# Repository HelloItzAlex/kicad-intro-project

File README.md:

# Kicad Intro Project

We will be creating an Astable timer circuit using a 555 timer, an LED, resistors, capacitors, and batteries. 555 timers can be used to generate stable and accurate oscillations or time delays. In our case, we will be using this [timer](https://www.ti.com/lit/ds/symlink/lm555.pdf?HQS=dis-dk-null-digikeymode-dsf-pf-null-wwe&ts=1630736989538&ref_url=https%253A%252F%252Fwww.ti.com%252Fgeneral%252Fdocs%252Fsuppproductinfo.tsp%253FdistId%253D10%2526gotoUrl%253Dhttps%253A%252F%252Fwww.ti.com%252Flit%252Fgpn%252Flm555)
 to run in Astable operation mode, which means that it will begin a free running oscillation. I recommend reading through the datasheet linked above, as lots of useful information can be found there! The frequency of the oscillations can be controlled by the value of resistors and capacitors that you choose to use in your circuit.  

The equation used to calculate the frequency is shown here:

## Create a new Kicad Project:
+ The documentation for Kicad can be found [here](https://docs.kicad.org/5.1/en/getting_started_in_kicad/getting_started_in_kicad.html), where there is a step-by-step tutorial on creating your first project.
+ Create a new project by clicking File->New->Project, and naming it.

## Create your schematic:
+ The first step to designing a PCB is creating the schematic. Open the Kicad Schematic software, “Eeschema”, by clicking on the button titled “Schematic Layout Editor”. Now you can begin to create your circuit!
+ There wil also be an example schematic included in the repository that can be used as a reference.
+ Begin placing components and wiring them together to create the circuit. Refer back to the [Kicad documentation](https://docs.kicad.org/5.1/en/getting_started_in_kicad/getting_started_in_kicad.html) for detailed instructions on how to place components and connect them together. All of  the components necessary for this tutorial are available in the Kicad component library. A list of the components you will need:
    + *1* LM555 Timer
    + *1* LED
    + *2* Resistors(1 10k Resistor, and 1 5k Resistor)
    + *2* Capacitors(1 0.01uF Capacitor, and 1 10uF Capacitor)
    + *2* 3V Single Cell Batteries
    + *2* VCC Labels
    + *2* GND Labels
    + *2* Power Flags
+  An example circuit for an Astable timer can be found in the datasheet(not including batteries):

+ Once you have finished making your circuit, run through these steps in order:
    1. Click on the Annotate Schematic symbol , and annotate all symbols in the schematic.
    2. Click on the Electrical Rules Check(ERC) symbol , and verify that you aren't violating any electrical rules.
    3. Click on the Assign PCB footprints to schematic symbol . Here, you will tell the PCB editor which physical footprint goes with each schematic symbol. It is up to you to make sure that the symbol has the corresponding footprint. The list of footprints that will be used:
        + *2* Battery:BatteryHolder_LINX_BAT-HLD-012-SMT
        + *2* Capacitor_SMD:C_0805_2012Metric
        + *2* Resistor_SMD:R_0805_2012Metric
        + *1* LED_SMD:LED_0805_2012Metric
        + *1* Package_SO:SOIC-8_3.9x4.9mm_P1.27mm (for the 555 timer)
    4. Click on the Generate Netlist symbol , and generate the netlist that will be used in the PCB editor, "PCBnew".
+ You have now finished with the Schematic design part of this project! Next, we will complete the PCB design in PCBnew

## Create your PCB Layout
+ Again, refer back to the [Kicad documentation](https://docs.kicad.org/5.1/en/getting_started_in_kicad/getting_started_in_kicad.html) for more detailed instructions on how to create a PCB Layout.
+ Click on the Pcbnew symbol  that will take you to the PCB editor.
+ We will be creating a two layer board, which is the default in Kicad. We will also be keeping the default track width and PCB thickness.
+ To load in the netlist that was previously generated, click on the same Load Netlist symbol . Find the netlist file that was generated and then click Update PCB. This will place all of the components on the page with a ratsnest connecting all the pins. You can move components around until you have a very rough initial layout. This does not have to be your final component placement, their position can always be moved.
+ To create a physical border for the PCB, make sure you have clicked on the layer labeled Edge.Cuts, and create a rectangle or square using the Graphic Polygon tool 
+ Make sure all of your components are inside your board outline, and then begin routing tracks between the different pins on your components. Once all the white lines of the ratsnest have disappeared, you'll know that all your components have been fully connected. Routing between many components can be challenging, don't be afraid to try mutliple paths until you are satisfied with your layout. Feel free to route on both sides of the board using vias if necessary.
+ Run the ERC  again to make sure everything is connected.
+ You can add text to both the front and back layers of your board by clicking on the Add Text symbol  and the corresponding layer, either F.SilkS or B.SilkS. The convention for boards is to include the title of the board, the designer's name, and the revision number.
+ Kicad allows you to view a 3D version of your board! Go to View->3D Viewer to see a 3D rendering.
+ Once you have finalized your layout, you can generate the Gerber files that will be uploaded to a PCB manufacturer's website. Click on the Plot symbol  and generate Gerber files in the folder of your choice. If you have mounting holes or vias on your board, generate the drill files as well.
+ You have completed the PCB design section of this project!
+ If interested, your PCB can possibly be ordered from JLCPCB and hand-soldered together. This is not a required part of the intro project.

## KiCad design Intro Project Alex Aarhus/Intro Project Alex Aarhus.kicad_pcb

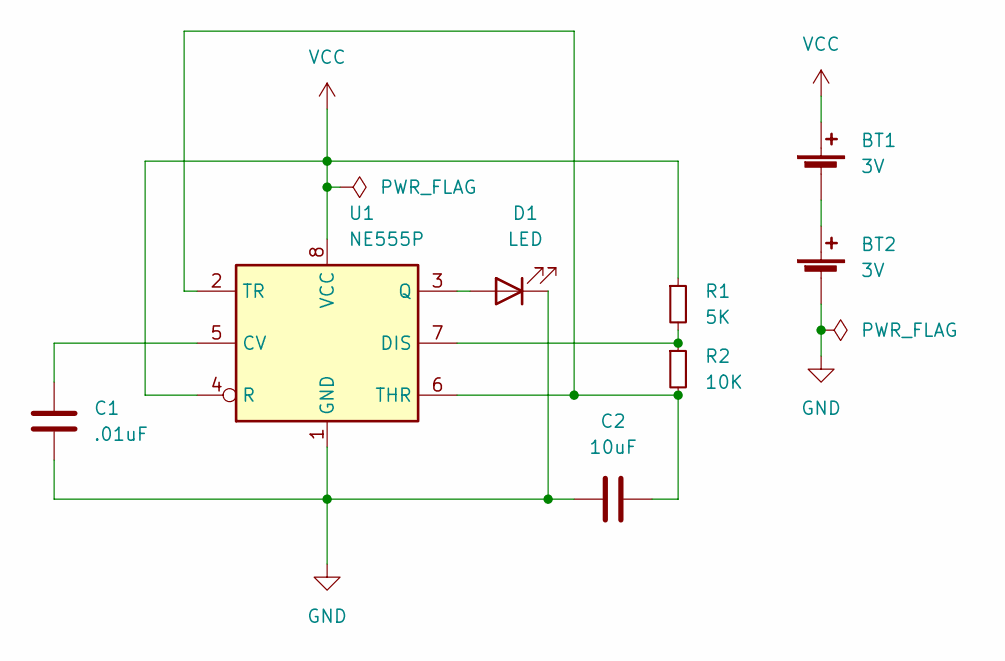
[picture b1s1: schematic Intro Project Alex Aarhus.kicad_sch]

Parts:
BT1, BT2: 3V; BatteryHolder_LINX_BAT-HLD-012-SMT
C1: .01uF; C_0805_2012Metric
C2: 10uF; C_0805_2012Metric
D1: LED; LED_0805_2012Metric
R1: 5K; R_0805_2012Metric
R2: 10K; R_0805_2012Metric
U1: NE555P; SOIC-8_3.9x4.9mm_P1.27mm

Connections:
GND: BT2.2 (-), C1.2, C2.1, D1.1 (K), U1.1 (GND)
unnamed: BT1.2 (-), BT2.1 (+)
unnamed: C1.1, U1.5 (CV)
unnamed: C2.2, R2.2, U1.2 (TR), U1.6 (THR)
unnamed: D1.2 (A), U1.3 (Q)
unnamed: R1.2, R2.1, U1.7 (DIS)
VCC: BT1.1 (+), R1.1, U1.4 (R), U1.8 (VCC)

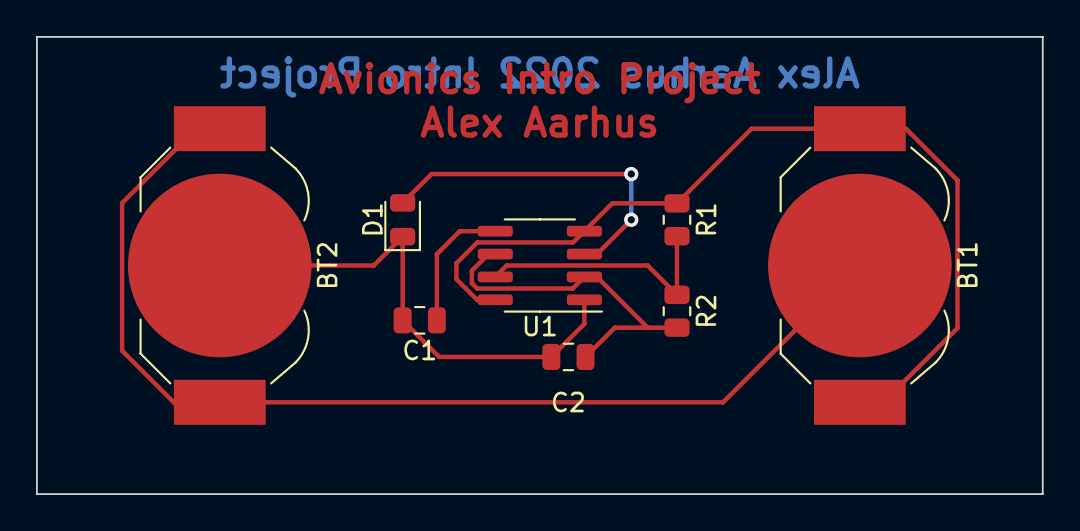
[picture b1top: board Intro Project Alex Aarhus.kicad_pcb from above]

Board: 2 copper layers, 55.9 x 25.4 mm, 8 parts (0 on the bottom side), 7 nets.

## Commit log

2022-09-17 Opened Files
    No change. Just opened for viewing
2022-09-18 Creation of Basic Intro Project
    Just creating a KiCad Project
2022-09-18 Started work on schematics
2022-09-19 Finished Intro Project
    Created and wired PCB board
    Created Gerber files
2022-09-19 Autosave
    Just opened no changes
2023-04-03 Random stuff
